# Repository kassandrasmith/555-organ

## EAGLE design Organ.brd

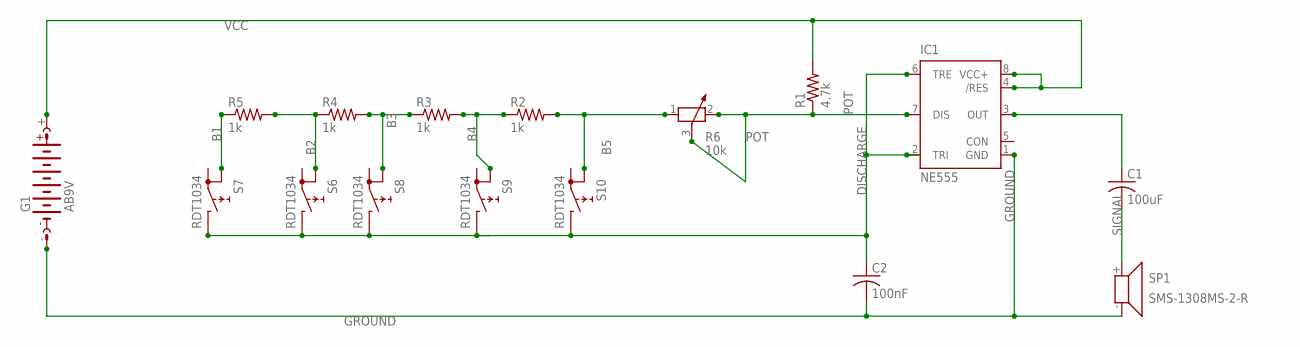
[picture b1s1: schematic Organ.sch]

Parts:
C1: 100uF; C0805
C2: 100nF; C0805
G1: AB9V
IC1: NE555; DIL-08
R1: 4.7k; R0805
R2, R3, R4, R5: 1k; R0805
R6: 10k; PT-10
S6, S7, S8, S9, S10: RDT1034
SP1: SMS-1308MS-2-R

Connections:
B1: R5.1, S7.A
B2: R4.1, R5.2, S6.A
B3: R3.1, R4.2, S8.A
B4: R2.1, R3.2, S9.A
B5: R2.2, R6.1, S10.A
DISCHARGE: C2.1, IC1.2 (TRI), IC1.6 (TRE), S6.B, S7.B, S8.B, S9.B, S10.B
GROUND: C2.2, G1.-, IC1.1 (GND), SP1.- (2)
unnamed: C1.1, IC1.3 (OUT)
POT: IC1.7 (DIS), R1.1, R6.2, R6.3
SIGNAL: C1.2, SP1.+ (1)
VCC: G1.+, IC1.4 (/RES), IC1.8 (VCC+), R1.2

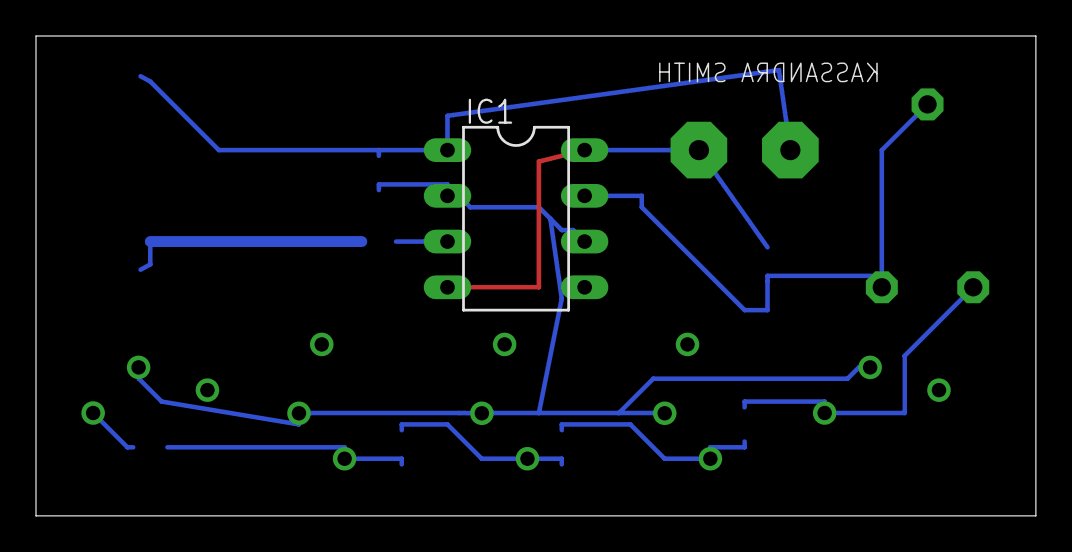
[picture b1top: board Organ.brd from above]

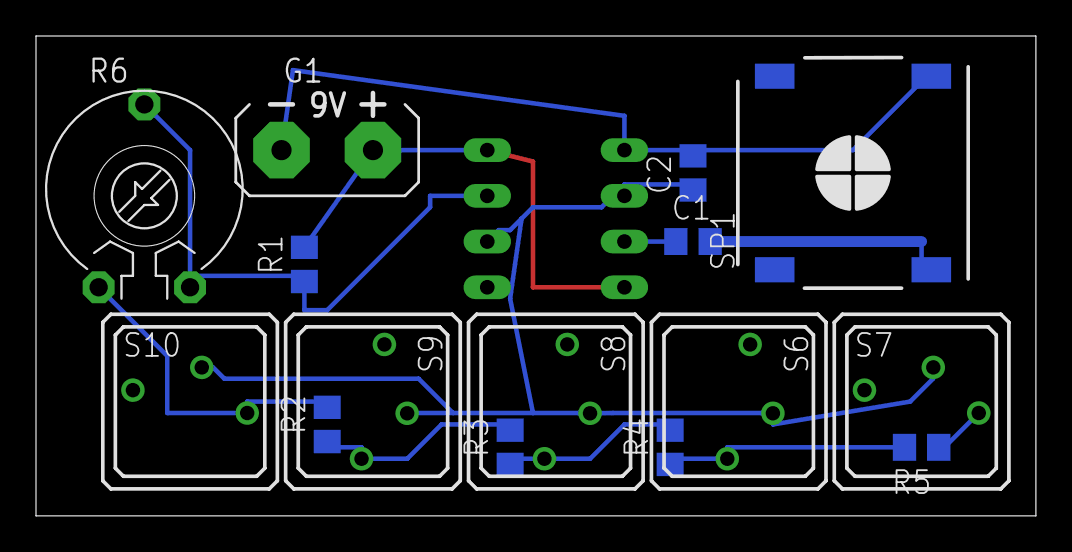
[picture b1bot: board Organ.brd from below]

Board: 2 copper layers, 55.5 x 26.7 mm, 16 parts (15 on the bottom side), 11 nets.

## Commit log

2015-02-10 :octocat: Added .gitattributes & .gitignore files
2015-02-10 Add 555 Timer Organ board
    Add initial PCB
    Add gitignore for superfluous eagle files
2015-02-10 Shink board footprint
    Make board smaller, less costly
2015-02-10 Add name
    Add name of maker
2015-02-10 Fix name
    Change layer name is on
2015-07-24 Use new sizing standards
